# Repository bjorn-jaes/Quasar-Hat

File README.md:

# Quasar-Hat

Project intented for creating a hat board for the ConnectTech Carrier board.
The board provides
- GPS, with external antenna
- Power reading
- Power button
- M12 power input
- M12 CAN bus input

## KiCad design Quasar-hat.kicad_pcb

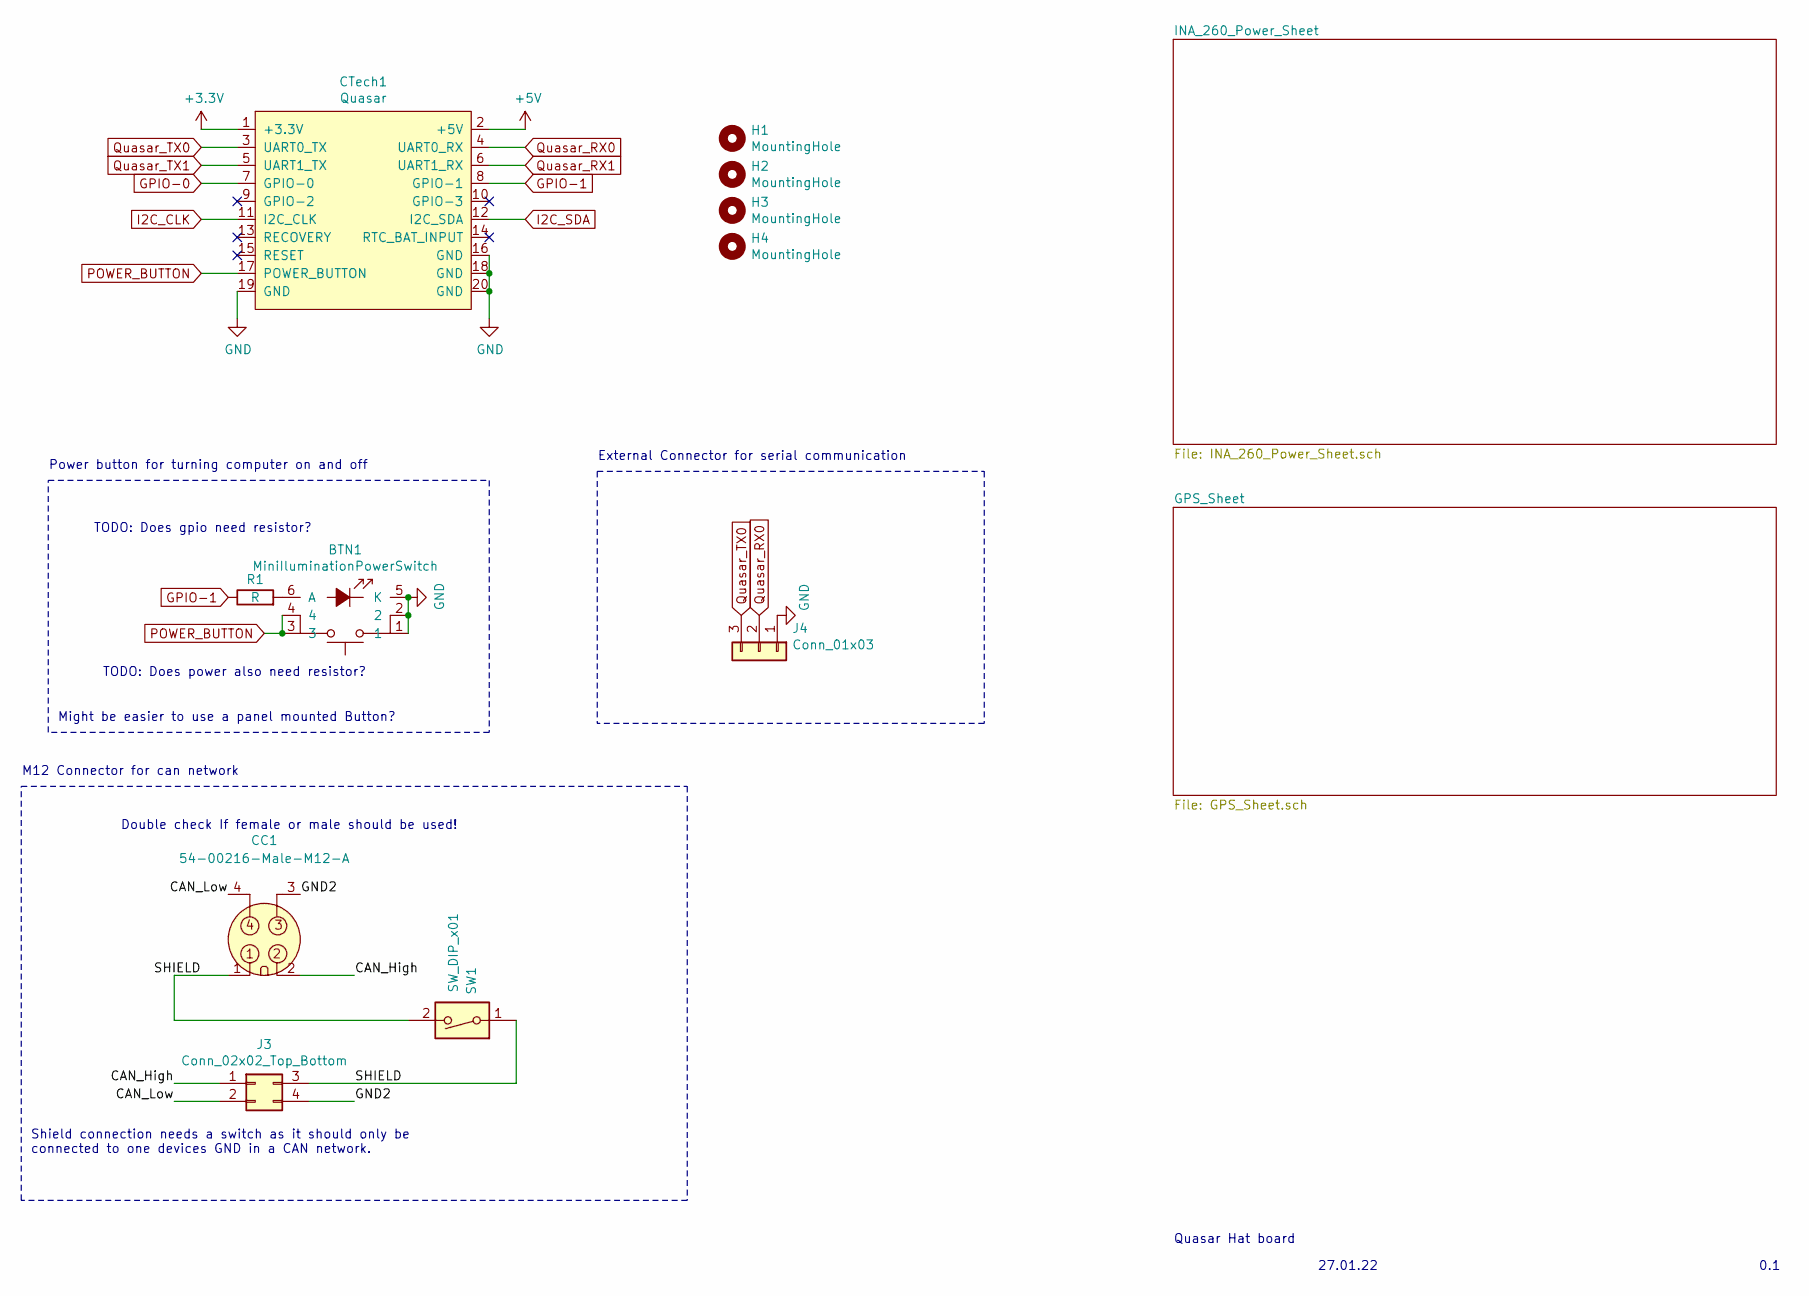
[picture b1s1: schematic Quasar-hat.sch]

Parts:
BTN1: MiniIluminationPowerSwitch; Led_Power_PushButton
CC1: 54-00216-Male-M12-A; Male-M12-Connecter
CTech1: Quasar; PinSocket_2x10_P2.54mm_Vertical
H1, H2, H3, H4: MountingHole; MountingHole_3mm
J3: Conn_02x02_Top_Bottom; PinSocket_2x02_P2.54mm_Vertical
J4: Conn_01x03; PinHeader_1x03_P2.54mm_Vertical
R1: R; R_0201_0603Metric
SW1: SW_DIP_x01; SW_DIP_SPSTx01_Slide_Copal_CHS-01A_W5.08mm_P1.27mm_JPin

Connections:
+3V3: CTech1.1 (+3.3V); also elsewhere on the board
+5V: CTech1.2 (+5V)
/CAN_High: CC1.2, J3.1
/CAN_Low: CC1.4, J3.2
/GND2: CC1.3, J3.4
/SHIELD: CC1.1, J3.3, SW1.1, SW1.2
GND: BTN1.1, BTN1.2, BTN1.5 (K), CTech1.16 (GND), CTech1.18 (GND), CTech1.19 (GND), CTech1.20 (GND), J4.1; also elsewhere on the board
GPIO-0: CTech1.7 (GPIO-0); also elsewhere on the board
GPIO-1: CTech1.8 (GPIO-1), R1.1
I2C_CLK: CTech1.11 (I2C_CLK); also elsewhere on the board
I2C_SDA: CTech1.12 (I2C_SDA); also elsewhere on the board
unnamed: BTN1.6 (A), R1.2
POWER_BUTTON: BTN1.3, BTN1.4, CTech1.17 (POWER_BUTTON)
Quasar_RX0: CTech1.4 (UART0_RX), J4.2
Quasar_RX1: CTech1.6 (UART1_RX); also elsewhere on the board
Quasar_TX0: CTech1.3 (UART0_TX), J4.3
Quasar_TX1: CTech1.5 (UART1_TX); also elsewhere on the board

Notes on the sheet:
Double check If female or male should be used!
Shield connection needs a switch as it should only be connected to one devices GND in a CAN network.
TODO: Does gpio need resistor?
TODO: Does power also need resistor?
External Connector for serial communication
27.01.22
Quasar Hat board
0.1
M12 Connector for can network
Power button for turning computer on and off
Might be easier to use a panel mounted Button?

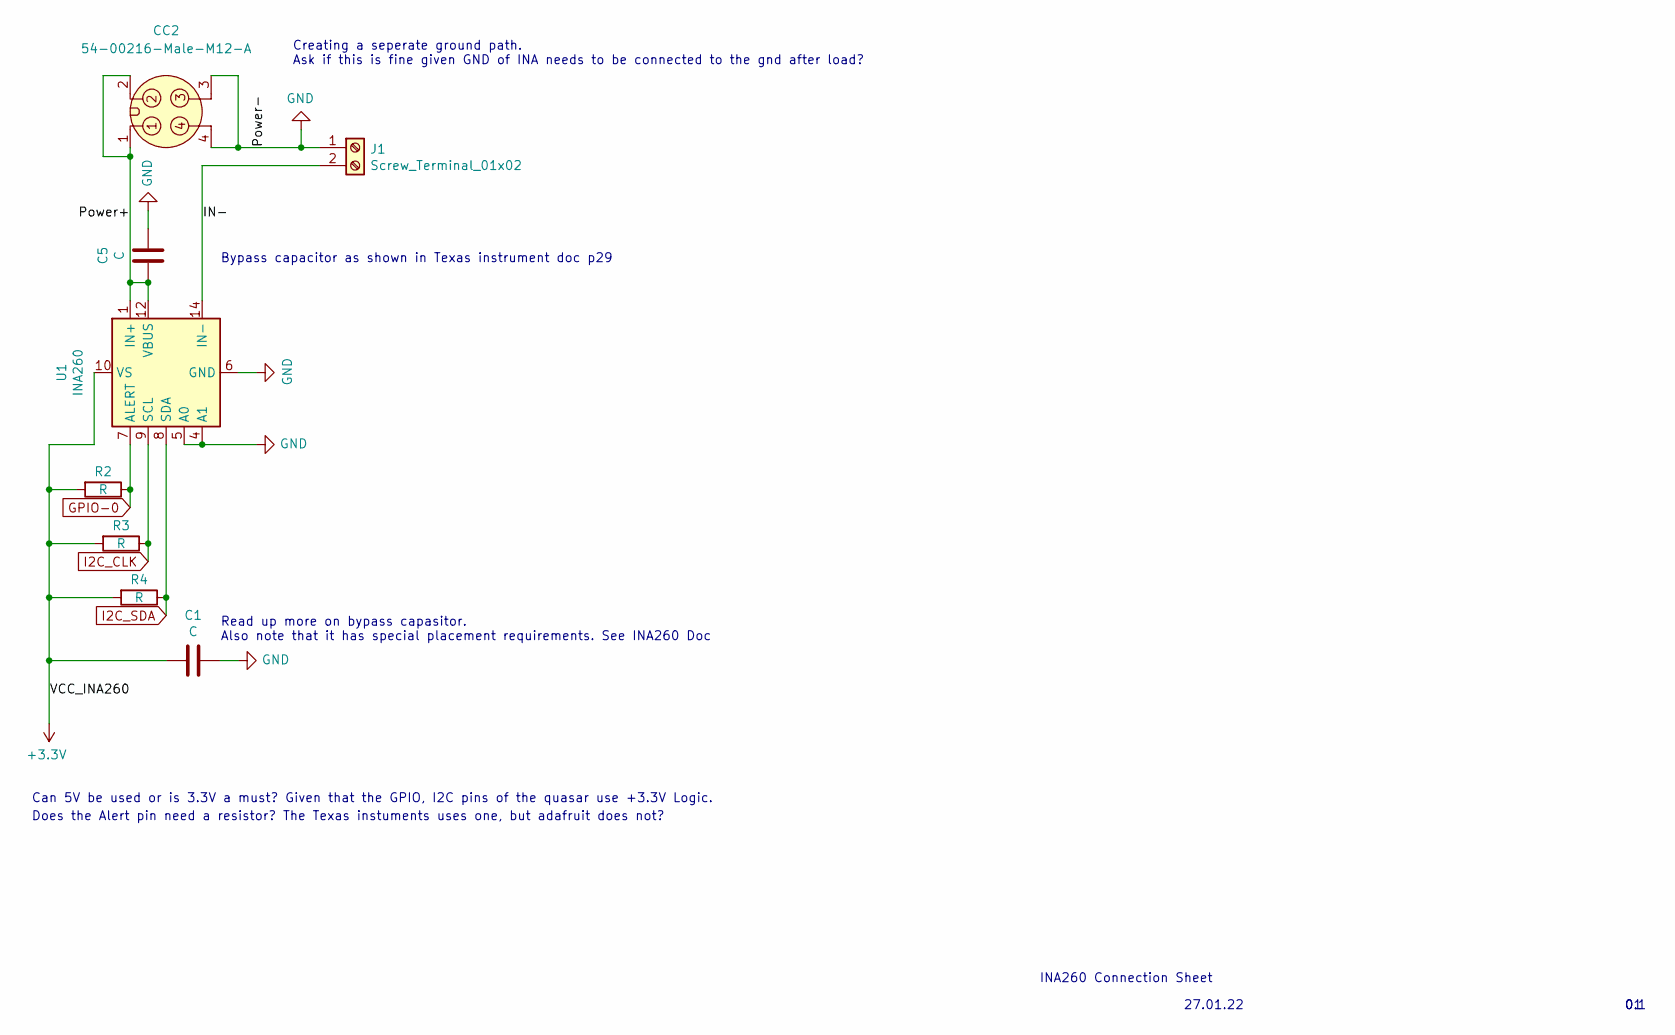
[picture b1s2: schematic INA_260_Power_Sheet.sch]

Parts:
C1, C5: C; C_0201_0603Metric
CC2: 54-00216-Male-M12-A; Male-M12-Connecter
J1: Screw_Terminal_01x02; TerminalBlock_4Ucon_1x02_P3.50mm_Horizontal
R2, R3, R4: R; R_0201_0603Metric
U1: INA260; TSSOP-16_4.4x5mm_P0.65mm

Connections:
+3V3: C1.1, R2.2, R3.2, R4.2, U1.10 (VS); also elsewhere on the board
/INA_260_Power_Sheet/IN-: J1.2, U1.14 (IN-), U1.15 (IN-), U1.16 (IN-)
/INA_260_Power_Sheet/Power+: C5.1, CC2.1, CC2.2, U1.1 (IN+), U1.2 (IN+), U1.3 (IN+), U1.12 (VBUS)
GND: C1.2, C5.2, CC2.3, CC2.4, J1.1, U1.4 (A1), U1.5 (A0), U1.6 (GND), U1.11 (GND); also elsewhere on the board
GPIO-0: R2.1, U1.7 (ALERT); also elsewhere on the board
I2C_CLK: R3.1, U1.9 (SCL); also elsewhere on the board
I2C_SDA: R4.1, U1.8 (SDA); also elsewhere on the board

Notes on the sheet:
Creating a seperate ground path. Ask if this is fine given GND of INA needs to be connected to the gnd after load?
Can 5V be used or is 3.3V a must? Given that the GPIO, I2C pins of the quasar use +3.3V Logic.
Does the Alert pin need a resistor? The Texas instuments uses one, but adafruit does not?
Read up more on bypass capasitor. Also note that it has special placement requirements. See INA260 Doc
Bypass capacitor as shown in Texas instrument doc p29
27.01.22
INA260 Connection Sheet
0.1

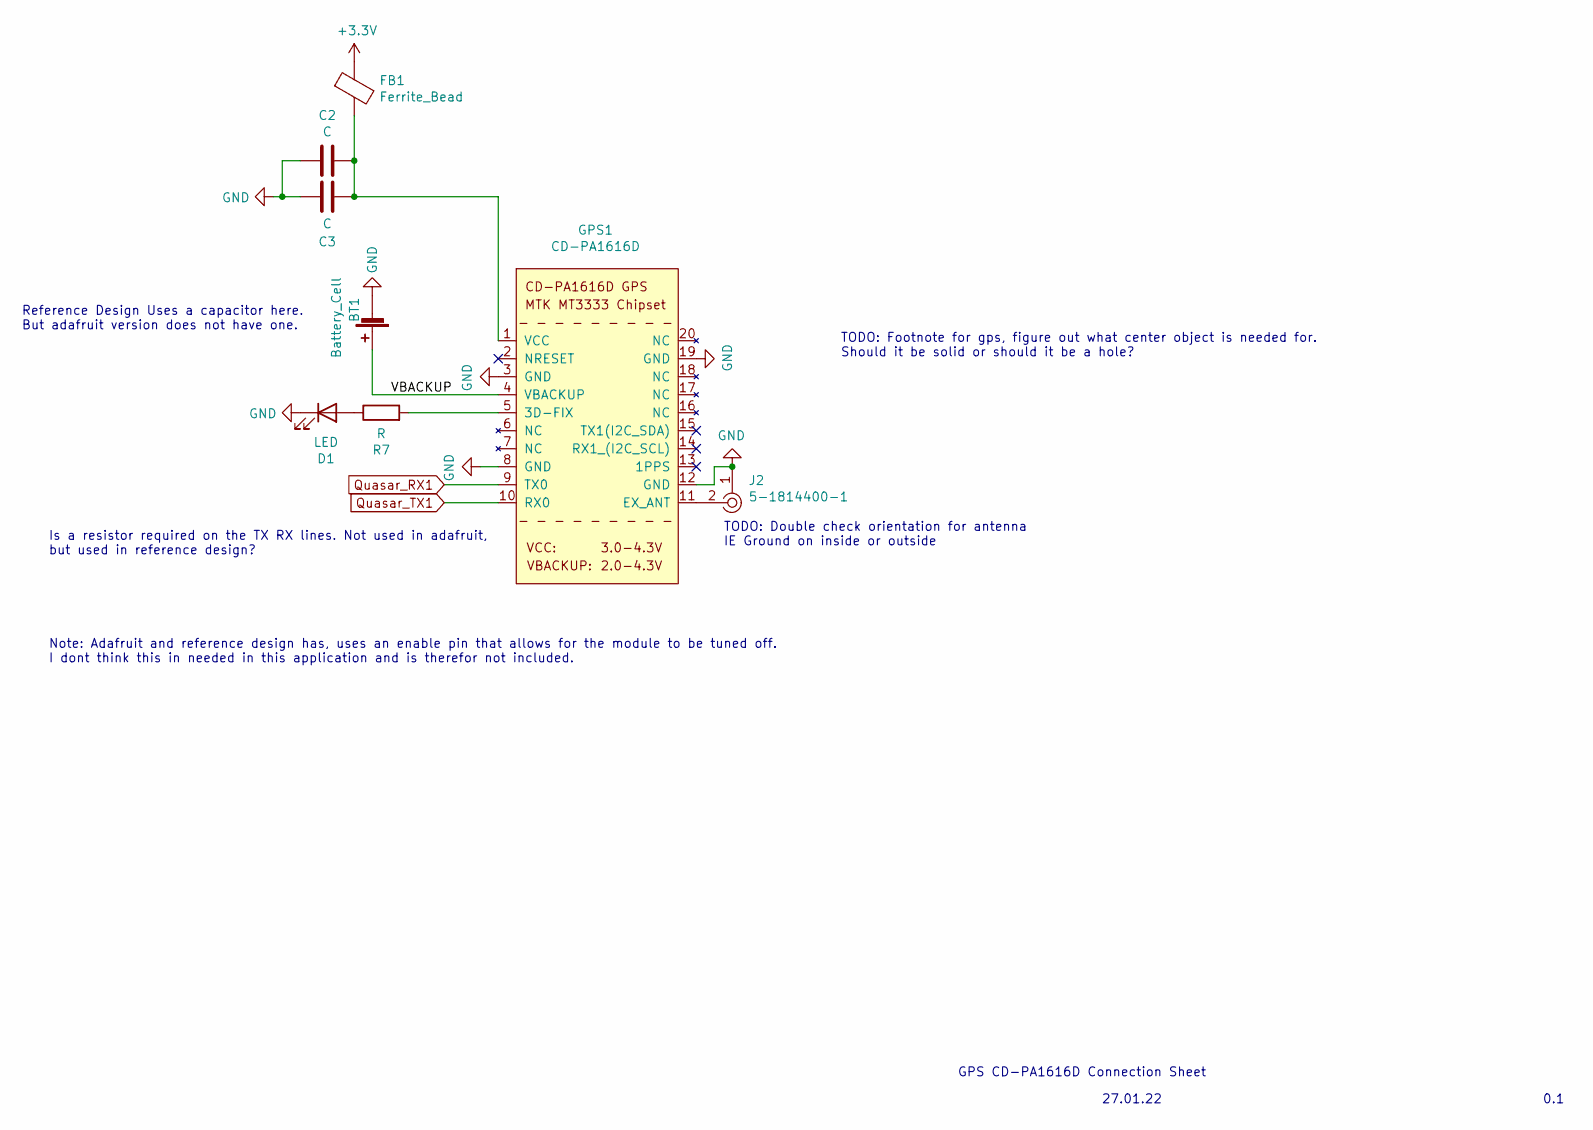
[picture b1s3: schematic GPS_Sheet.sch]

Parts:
BT1: Battery_Cell; BatteryHolder_Keystone_3000_1x12mm
C2, C3: C; C_0201_0603Metric
D1: LED; LED_0201_0603Metric
FB1: Ferrite_Bead; L_0201_0603Metric
GPS1: CD-PA1616D
J2: 5-1814400-1; SMA_Amphenol_132134-11_Vertical; MPN 5-1814400-1; Digi-Key_PN A97593-ND
R7: R; R_0201_0603Metric

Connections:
+3V3: FB1.1; also elsewhere on the board
/GPS_Sheet/VBACKUP: BT1.1 (+), GPS1.4 (VBACKUP)
GND: BT1.2 (-), C2.1, C3.1, D1.1 (K), GPS1.3 (GND), GPS1.8 (GND), GPS1.12 (GND), GPS1.19 (GND), J2.1; also elsewhere on the board
unnamed: C2.2, C3.2, FB1.2, GPS1.1 (VCC)
unnamed: D1.2 (A), R7.1
unnamed: GPS1.5 (3D-FIX), R7.2
unnamed: GPS1.11 (EX_ANT), J2.2
Quasar_RX1: GPS1.9 (TX0); also elsewhere on the board
Quasar_TX1: GPS1.10 (RX0); also elsewhere on the board

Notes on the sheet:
Is a resistor required on the TX RX lines. Not used in adafruit, but used in reference design?
Note: Adafruit and reference design has, uses an enable pin that allows for the module to be tuned off. I dont think this in needed in this application and is therefor not included.
TODO: Footnote for gps, figure out what center object is needed for. Should it be solid or should it be a hole?
TODO: Double check orientation for antenna IE Ground on inside or outside
Reference Design Uses a capacitor here. But adafruit version does not have one.
27.01.22
GPS CD-PA1616D Connection Sheet
0.1

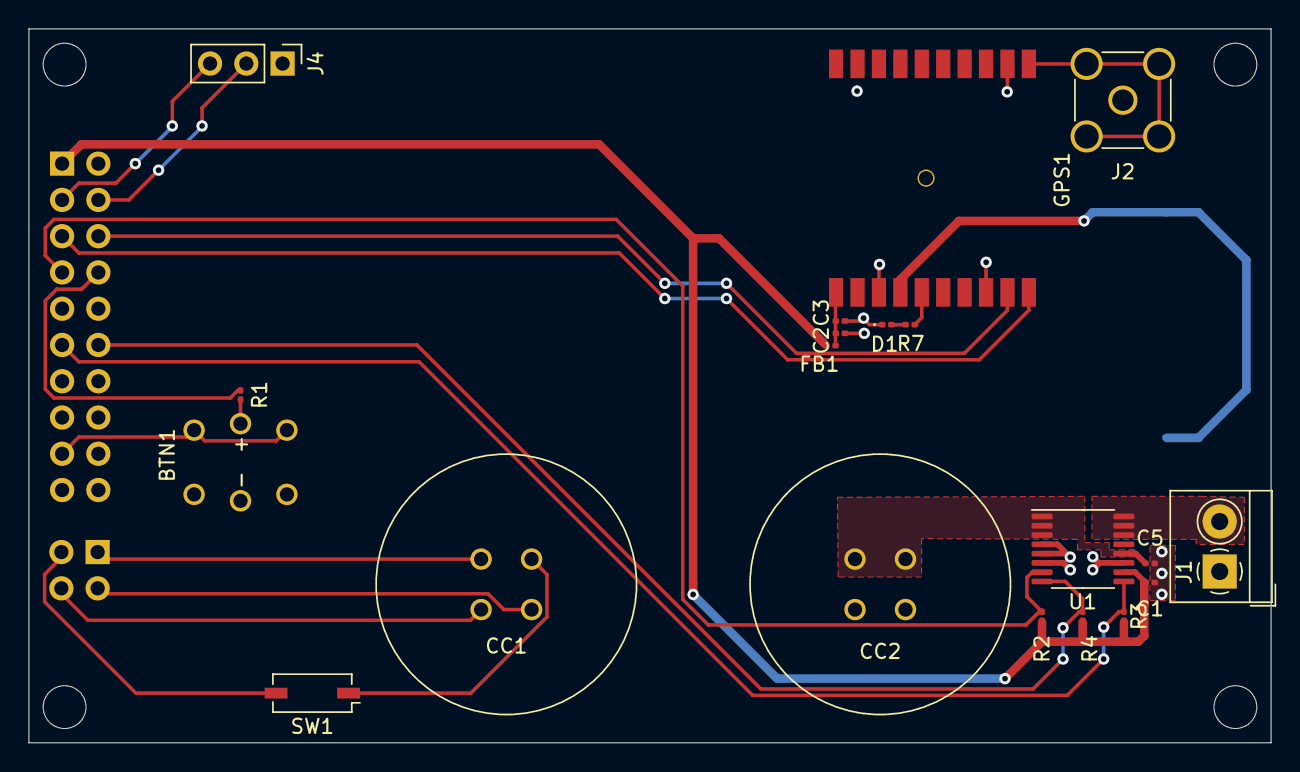
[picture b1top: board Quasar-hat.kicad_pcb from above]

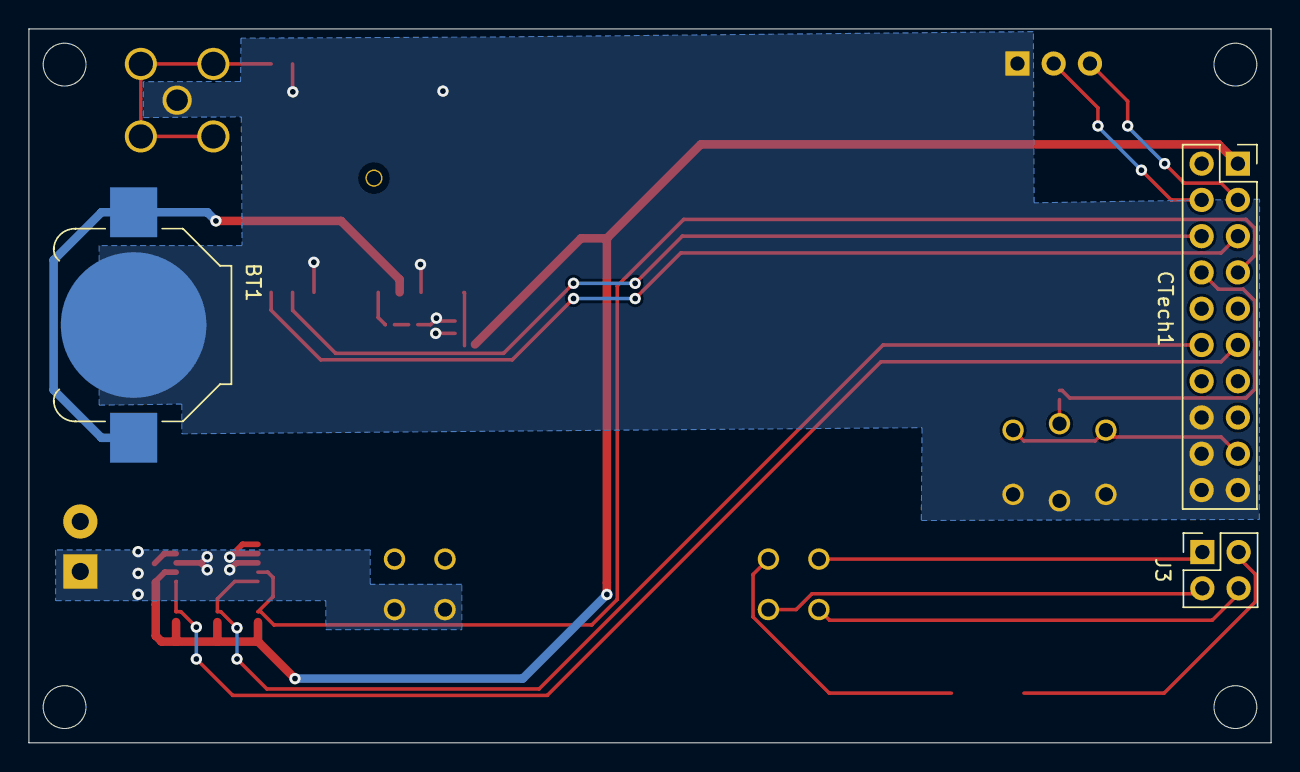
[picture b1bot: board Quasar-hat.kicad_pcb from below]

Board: 2 copper layers, 87.0 x 50.0 mm, 27 parts (3 on the bottom side), 23 nets.

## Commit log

2022-01-27 Inital version of hat
